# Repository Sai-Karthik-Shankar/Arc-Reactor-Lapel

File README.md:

# Arc-Reactor-Lapel

Fabric is so last year. Arc Reactor Lapel is a modern piece of clothing that can brighten the whole attire up.

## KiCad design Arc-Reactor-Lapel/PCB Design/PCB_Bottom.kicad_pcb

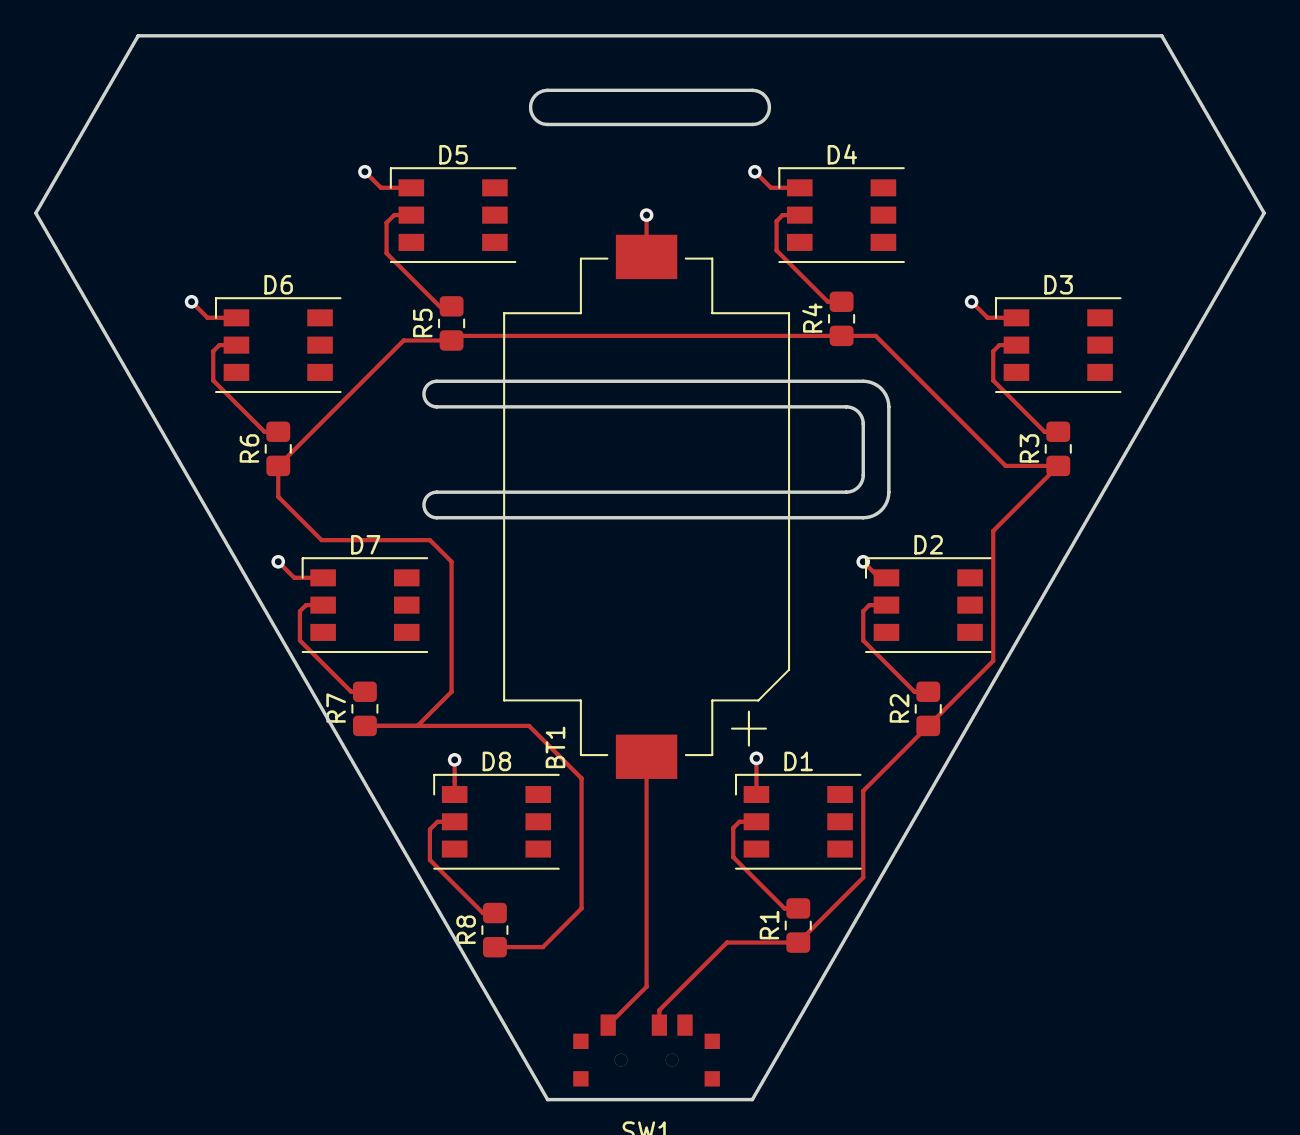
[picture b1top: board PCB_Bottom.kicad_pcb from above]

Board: 2 copper layers, 72.0 x 62.4 mm, 18 parts (0 on the bottom side), 11 nets.

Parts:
BT1: Battery_Cell; BatteryHolder_Keystone_1060_1x2032
D1, D2, D3, D4, D5, D6, D7, D8: LED; LED_WS2812_PLCC6_5.0x5.0mm_P1.6mm
R1, R2, R3, R4, R5, R6, R7, R8: R; R_0805_2012Metric_Pad1.20x1.40mm_HandSolder
SW1: SW_SPST; sw_slide_7x3

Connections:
GND: BT1.2, D1.1, D2.1, D3.1, D4.1, D5.1, D6.1, D7.1, D8.1
unnamed: BT1.1, SW1.1
unnamed: D1.2, R1.2
unnamed: D2.2, R2.2
unnamed: D3.2, R3.2
unnamed: D4.2, R4.2
unnamed: D5.2, R5.2
unnamed: D6.2, R6.2
unnamed: D7.2, R7.2
unnamed: D8.2, R8.2
unnamed: R1.1, R2.1, R3.1, R4.1, R5.1, R6.1, R7.1, R8.1, SW1.2
